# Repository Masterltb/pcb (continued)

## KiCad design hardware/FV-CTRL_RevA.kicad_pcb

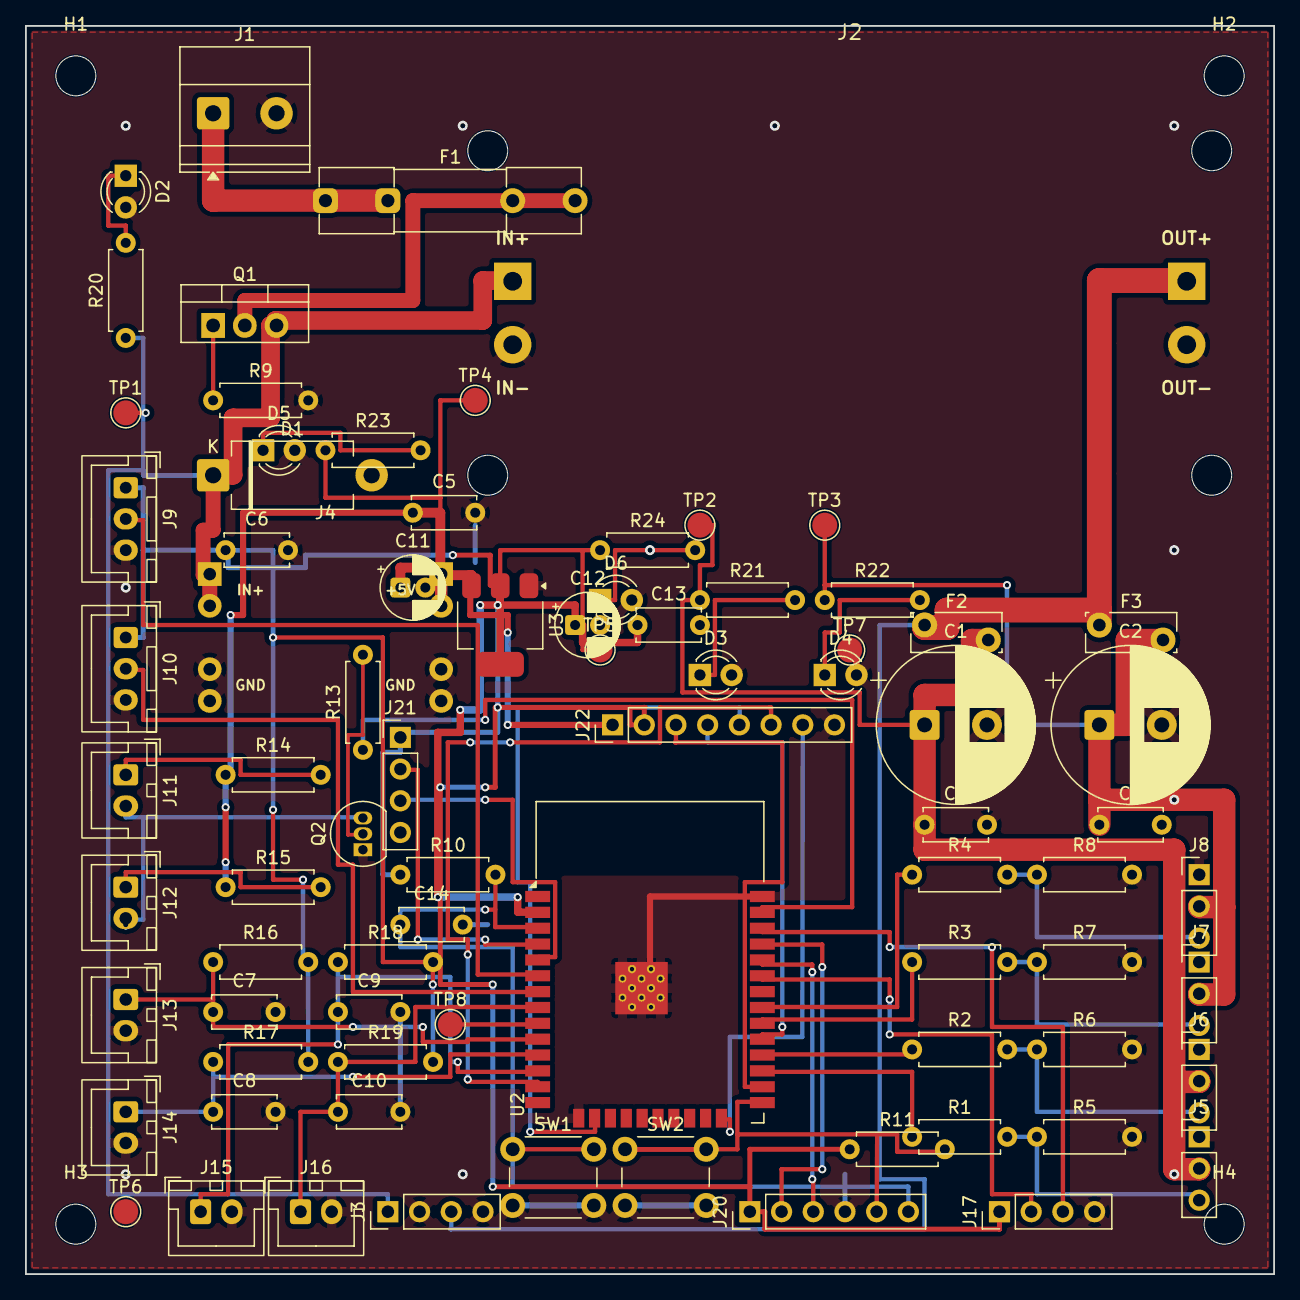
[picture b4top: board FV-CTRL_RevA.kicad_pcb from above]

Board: 2 copper layers, 100.0 x 100.0 mm, 84 parts (0 on the bottom side), 48 nets.

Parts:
C1, C2: 1000-2200uF 16V; CP_Radial_D12.5mm_P5.00mm
C3, C4, C6, C13, C14: 100nF; C_Disc_D5.0mm_W2.5mm_P5.00mm
C5: 10uF 16V; C_Disc_D5.0mm_W2.5mm_P5.00mm
C7, C8, C9, C10: 100nF (DNP); C_Disc_D5.0mm_W2.5mm_P5.00mm
C11: 10uF 16V; CP_Radial_D5.0mm_P2.00mm
C12: 22uF 16V; CP_Radial_D5.0mm_P2.00mm
D1: 1.5KE15CA; D_DO-201_P12.70mm_Horizontal
D2: LED_+12V; LED_D3.0mm
D3: LED_+6V_A; LED_D3.0mm
D4: LED_+6V_B; LED_D3.0mm
D5: LED_+5V; LED_D3.0mm
D6: LED_+3V3; LED_D3.0mm
F1: 5A 250V; Fuseholder_Clip-5x20mm_Littelfuse_111_Inline_P20.00x5.00mm_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
F2, F3: PTC 3A; Fuse_Bourns_MF-RG300
H1, H2, H3, H4: MountingHole_3.2mm_M3
J1: 12V_IN; TerminalBlock_Phoenix_MKDS-1,5-2-5.08_1x02_P5.08mm_Horizont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
J2: XH-M401 (6.0V 8A); Converter_DCDC_XH-M401_8A
J3: AUX_BUCK (DNP); PinHeader_1x04_P2.54mm_Vertical
J4: MP1584EN (5V Logic); Converter_DCDC_MP1584EN
J5: S1_TOP; PinHeader_1x03_P2.54mm_Vertical
J6: S1_BOT; PinHeader_1x03_P2.54mm_Vertical
J7: S2_TOP; PinHeader_1x03_P2.54mm_Vertical
J8: S2_BOT; PinHeader_1x03_P2.54mm_Vertical
J9: IR_RX1; JST_XH_B3B-XH-A_1x03_P2.50mm_Vertical
J10: IR_RX2; JST_XH_B3B-XH-A_1x03_P2.50mm_Vertical
J11: IR_TX1 (Col 1); JST_XH_B2B-XH-A_1x02_P2.50mm_Vertical
J12: IR_TX2 (Col 2); JST_XH_B2B-XH-A_1x02_P2.50mm_Vertical
J13: LS1 (DNP); JST_XH_B2B-XH-A_1x02_P2.50mm_Vertical
J14: LS2 (DNP); JST_XH_B2B-XH-A_1x02_P2.50mm_Vertical
J15: LS3 (DNP); JST_XH_B2B-XH-A_1x02_P2.50mm_Vertical
J16: LS4 (DNP); JST_XH_B2B-XH-A_1x02_P2.50mm_Vertical
J17: I2C_RESERVED; PinHeader_1x04_P2.54mm_Vertical
J20: PROG_UART0; PinHeader_1x06_P2.54mm_Vertical
J21: SENSOR_ADC; PinHeader_1x04_P2.54mm_Vertical
J22: SENSOR_DIGITAL; PinHeader_1x08_P2.54mm_Vertical
Q1: IRF9540N; TO-220-3_Vertical
Q2: S8050; TO-92_Inline
R1, R2, R3, R4: 330R; R_Axial_DIN0207_L6.3mm_D2.5mm_P7.62mm_Horizontal
R5, R6, R7, R8, R9, R10, R11: 10k; R_Axial_DIN0207_L6.3mm_D2.5mm_P7.62mm_Horizontal
R13: 1k; R_Axial_DIN0207_L6.3mm_D2.5mm_P7.62mm_Horizontal
R14, R15: 120R; R_Axial_DIN0207_L6.3mm_D2.5mm_P7.62mm_Horizontal
R16, R17, R18, R19: 10k (DNP); R_Axial_DIN0207_L6.3mm_D2.5mm_P7.62mm_Horizontal
R20: 5.6k; R_Axial_DIN0207_L6.3mm_D2.5mm_P7.62mm_Horizontal
R21, R22: 2.2k; R_Axial_DIN0207_L6.3mm_D2.5mm_P7.62mm_Horizontal
R23: 1.5k; R_Axial_DIN0207_L6.3mm_D2.5mm_P7.62mm_Horizontal
R24: 1.0k; R_Axial_DIN0207_L6.3mm_D2.5mm_P7.62mm_Horizontal
SW1: SW_EN; SW_PUSH_6mm_H5mm
SW2: SW_BOOT; SW_PUSH_6mm_H5mm
TP1: TP_+12V; TestPoint_Pad_D2.0mm
TP2: TP_+6V_A; TestPoint_Pad_D2.0mm
TP3: TP_+6V_B; TestPoint_Pad_D2.0mm
TP4: TP_+5V; TestPoint_Pad_D2.0mm
TP5: TP_+3V3; TestPoint_Pad_D2.0mm
TP6, TP7: TP_GND; TestPoint_Pad_D2.0mm
TP8: TP_SPARE_GPIO33; TestPoint_Pad_D2.0mm
U2: ESP32-WROOM-32; ESP32-WROOM-32_HandSolder
U3: AMS1117-3.3; SOT-223-3_TabPin2

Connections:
+3V3: C6.1, C12.1, C13.1, J9.1, J10.1, J17.1, J20.1, J21.1, J22.2, R10.1, R11.1, R16.2, R17.2, R18.2, R19.2, R24.1, TP5.1, U2.2, U3.2
+5V: C5.1, C11.1, J4.3, J22.1, R14.1, R15.1, R23.1, TP4.1, U3.3
+6V_A: C1.1, C3.1, F2.2, J5.2, J6.2, R21.1, TP2.1
+6V_B: C2.1, C4.1, F3.2, J7.2, J8.2, R22.1, TP3.1
+6V_SERVO: F2.1, F3.1, J2.3, J3.3
+12V: D1.1, J2.1, J3.1, J4.1, Q1.3, R20.1, TP1.1
+12V_FUSED: F1.2, Q1.2
+12V_IN: F1.1, J1.1
ADC_VN: J21.3, U2.5
ADC_VP: J21.2, U2.4
ESP_EN: C14.1, J20.6, R10.2, SW1.1, U2.3
ESP_IO0: J20.5, R11.2, SW2.1, U2.25
ESP_IR_TX: R13.1, U2.37
ESP_RXD0: J20.3, U2.34
ESP_S1_BOT_PWM: R2.1, U2.28
ESP_S1_TOP_PWM: R1.1, U2.27
ESP_S2_BOT_PWM: R4.1, U2.31
ESP_S2_TOP_PWM: R3.1, U2.30
ESP_TXD0: J20.2, U2.35
EXP_IO2: J22.7, U2.24
EXP_IO4: J22.3, U2.26
EXP_IO5: J22.4, U2.29
EXP_IO13: J22.5, U2.16
EXP_IO14: J22.6, U2.13
GND: C1.2, C2.2, C3.2, C4.2, C5.2, C6.2, C7.2, C8.2, C9.2, C10.2, C11.2, C12.2, C13.2, C14.2, D1.2, D2.2, D3.2, D4.2, D5.2, D6.2, J1.2, J2.2, J2.4, J3.2, J3.4, J4.2, J4.4, J5.1, J6.1, J7.1, J8.1, J9.3, J10.3, J13.2, J14.2, J15.2, J16.2, J17.4, J20.4, J21.4, J22.8, Q2.1, R5.2, R6.2, R7.2, R8.2, R9.2, SW1.2, SW2.2, TP6.1, TP7.1, U2.1, U2.15, U2.38, U2.39, U3.1
I2C_SCL: J17.3, U2.36
I2C_SDA: J17.2, U2.33
IR_RX1: J9.2, U2.6
IR_RX2: J10.2, U2.7
IR_TX_RET: J11.2, J12.2, Q2.3
LS1: C7.1, J13.1, R16.1, U2.10
LS2: C8.1, J14.1, R17.1, U2.11
LS3: C9.1, J15.1, R18.1, U2.12
LS4: C10.1, J16.1, R19.1, U2.8
NET_D2_ANODE: D2.1, R20.2
NET_D3_ANODE: D3.1, R21.2
NET_D4_ANODE: D4.1, R22.2
NET_D5_ANODE: D5.1, R23.2
NET_D6_ANODE: D6.1, R24.2
NET_IR_TX1_ANODE: J11.1, R14.2
NET_IR_TX2_ANODE: J12.1, R15.2
NET_Q1_GATE: Q1.1, R9.1
NET_Q2_BASE: Q2.2, R13.2
S1_BOT_PWM: J6.3, R2.2, R6.1
S1_TOP_PWM: J5.3, R1.2, R5.1
S2_BOT_PWM: J8.3, R4.2, R8.1
S2_TOP_PWM: J7.3, R3.2, R7.1
SPARE_GPIO33: TP8.1, U2.9

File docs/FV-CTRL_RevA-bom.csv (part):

Reference,Value,Footprint,DNP,Description,MPN
J1,12V_IN,"TerminalBlock_Phoenix:TerminalBlock_Phoenix_MKDS-1,5-2-5.08_1x02_P5.08mm_Horizontal",No,12V DC input pluggable screw terminal,Pluggable 2-pin 5.0mm
F1,5A 250V,Fuse:Fuseholder_Clip-5x20mm_Littelfuse_111_Inline_P20.00x5.00mm_D1.05mm_Horizontal,No,5A replaceable cartridge fuse in THT socket,5x20mm 5A cartridge
Q1,IRF9540N,Package_TO_SOT_THT:TO-220-3_Vertical,No,P-MOSFET reverse polarity protection,IRF9540NPBF
R9,10k,Resistor_THT:R_Axial_DIN0207_L6.3mm_D2.5mm_P7.62mm_Horizontal,No,P-MOSFET gate-to-GND pull-down resistor,10k 1/4W 5%
D1,1.5KE15CA,Diode_THT:D_DO-201_P12.70mm_Horizontal,No,12V bidirectional TVS overvoltage clamp,1.5KE15CA
J2,XH-M401 (6.0V 8A),fv_modules:Converter_DCDC_XH-M401_8A,No,"XH-M401 (6.0V 8A) header (IN+, IN-, OUT+, OUT-)",XH-M401 (XL4016E1 8A 200W)
J3,AUX_BUCK (DNP),Connector_PinHeader_2.54mm:PinHeader_1x04_P2.54mm_Vertical,Yes,"AUX_BUCK (DNP) header (IN+, IN-, OUT+, OUT-)",Auxiliary 4-pin Header
J4,MP1584EN (5V Logic),fv_modules:Converter_DCDC_MP1584EN,No,"MP1584EN (5V Logic) header (IN+, IN-, OUT+, OUT-)",MP1584EN Mini 3A Buck
F2,PTC 3A,Fuse:Fuse_Bourns_MF-RG300,No,Resettable PTC fuse for Servo Rail A (~3A hold),Bourns MF-R300
C1,1000-2200uF 16V,Capacitor_THT:CP_Radial_D12.5mm_P5.00mm,No,Bulk servo filter capacitor (Rail A),1000uF 16V Radial
C3,100nF,Capacitor_THT:C_Disc_D5.0mm_W2.5mm_P5.00mm,No,High-frequency decoupling (Rail A),100nF 50V Ceramic
J5,S1_TOP,Connector_PinHeader_2.54mm:PinHeader_1x03_P2.54mm_Vertical,No,"Column 1 Top Servo Header (GND, V+, SIG)",3-pin Header
J6,S1_BOT,Connector_PinHeader_2.54mm:PinHeader_1x03_P2.54mm_Vertical,No,"Column 1 Bottom Servo Header (GND, V+, SIG)",3-pin Header
F3,PTC 3A,Fuse:Fuse_Bourns_MF-RG300,No,Resettable PTC fuse for Servo Rail B (~3A hold),Bourns MF-R300
C2,1000-2200uF 16V,Capacitor_THT:CP_Radial_D12.5mm_P5.00mm,No,Bulk servo filter capacitor (Rail B),1000uF 16V Radial
C4,100nF,Capacitor_THT:C_Disc_D5.0mm_W2.5mm_P5.00mm,No,High-frequency decoupling (Rail B),100nF 50V Ceramic
J7,S2_TOP,Connector_PinHeader_2.54mm:PinHeader_1x03_P2.54mm_Vertical,No,"Column 2 Top Servo Header (GND, V+, SIG)",3-pin Header
J8,S2_BOT,Connector_PinHeader_2.54mm:PinHeader_1x03_P2.54mm_Vertical,No,"Column 2 Bottom Servo Header (GND, V+, SIG)",3-pin Header
J18,ESP32_Left (Pins 1-19),Connector_PinSocket_2.54mm:PinSocket_1x19_P2.54mm_Vertical,No,ESP32 DevKit 38 Left 19-pin Socket Header,19-pin Female Header 2.54mm
J19,ESP32_Right (Pins 20-38),Connector_PinSocket_2.54mm:PinSocket_1x19_P2.54mm_Vertical,No,ESP32 DevKit 38 Right 19-pin Socket Header,19-pin Female Header 2.54mm
R1,330R,Resistor_THT:R_Axial_DIN0207_L6.3mm_D2.5mm_P7.62mm_Horizontal,No,330 ohm series protection for S1_TOP_PWM,330R 1/4W 5%
R5,10k,Resistor_THT:R_Axial_DIN0207_L6.3mm_D2.5mm_P7.62mm_Horizontal,No,10k pull-down boot protection for S1_TOP_PWM,10k 1/4W 5%
R2,330R,Resistor_THT:R_Axial_DIN0207_L6.3mm_D2.5mm_P7.62mm_Horizontal,No,330 ohm series protection for S1_BOT_PWM,330R 1/4W 5%
R6,10k,Resistor_THT:R_Axial_DIN0207_L6.3mm_D2.5mm_P7.62mm_Horizontal,No,10k pull-down boot protection for S1_BOT_PWM,10k 1/4W 5%
R3,330R,Resistor_THT:R_Axial_DIN0207_L6.3mm_D2.5mm_P7.62mm_Horizontal,No,330 ohm series protection for S2_TOP_PWM,330R 1/4W 5%
R7,10k,Resistor_THT:R_Axial_DIN0207_L6.3mm_D2.5mm_P7.62mm_Horizontal,No,10k pull-down boot protection for S2_TOP_PWM,10k 1/4W 5%
R4,330R,Resistor_THT:R_Axial_DIN0207_L6.3mm_D2.5mm_P7.62mm_Horizontal,No,330 ohm series protection for S2_BOT_PWM,330R 1/4W 5%
R8,10k,Resistor_THT:R_Axial_DIN0207_L6.3mm_D2.5mm_P7.62mm_Horizontal,No,10k pull-down boot protection for S2_BOT_PWM,10k 1/4W 5%
R13,1k,Resistor_THT:R_Axial_DIN0207_L6.3mm_D2.5mm_P7.62mm_Horizontal,No,Base current limit resistor for IR driver,1k 1/4W 5%
Q2,S8050,Package_TO_SOT_THT:TO-92_Inline,No,NPN driver transistor for 38kHz IR burst transmitter,S8050
R14,120R,Resistor_THT:R_Axial_DIN0207_L6.3mm_D2.5mm_P7.62mm_Horizontal,No,Current limiting resistor for Col 1 IR LED,120R 1/2W 5%
J11,IR_TX1 (Col 1),Connector_JST:JST_XH_B2B-XH-A_1x02_P2.50mm_Vertical,No,Col 1 IR LED Emitter JST-XH 2-pin,JST-XH 2-pin
R15,120R,Resistor_THT:R_Axial_DIN0207_L6.3mm_D2.5mm_P7.62mm_Horizontal,No,Current limiting resistor for Col 2 IR LED,120R 1/2W 5%
J12,IR_TX2 (Col 2),Connector_JST:JST_XH_B2B-XH-A_1x02_P2.50mm_Vertical,No,Col 2 IR LED Emitter JST-XH 2-pin,JST-XH 2-pin
J9,IR_RX1,Connector_JST:JST_XH_B3B-XH-A_1x03_P2.50mm_Vertical,No,"Col 1 IR Receiver header (3V3, OUT, GND)",JST-XH 3-pin
J10,IR_RX2,Connector_JST:JST_XH_B3B-XH-A_1x03_P2.50mm_Vertical,No,"Col 2 IR Receiver header (3V3, OUT, GND)",JST-XH 3-pin
J13,LS1 (DNP),Connector_JST:JST_XH_B2B-XH-A_1x02_P2.50mm_Vertical,Yes,Limit switch LS1 (DNP),JST-XH 2-pin
R16,10k (DNP),Resistor_THT:R_Axial_DIN0207_L6.3mm_D2.5mm_P7.62mm_Horizontal,Yes,10k pull-up for LS1 (DNP),10k 1/4W 5%
C7,100nF (DNP),Capacitor_THT:C_Disc_D5.0mm_W2.5mm_P5.00mm,Yes,100nF filter capacitor for LS1 (DNP),100nF 50V Ceramic
J14,LS2 (DNP),Connector_JST:JST_XH_B2B-XH-A_1x02_P2.50mm_Vertical,Yes,Limit switch LS2 (DNP),JST-XH 2-pin
R17,10k (DNP),Resistor_THT:R_Axial_DIN0207_L6.3mm_D2.5mm_P7.62mm_Horizontal,Yes,10k pull-up for LS2 (DNP),10k 1/4W 5%
C8,100nF (DNP),Capacitor_THT:C_Disc_D5.0mm_W2.5mm_P5.00mm,Yes,100nF filter capacitor for LS2 (DNP),100nF 50V Ceramic
J15,LS3 (DNP),Connector_JST:JST_XH_B2B-XH-A_1x02_P2.50mm_Vertical,Yes,Limit switch LS3 (DNP),JST-XH 2-pin
R18,10k (DNP),Resistor_THT:R_Axial_DIN0207_L6.3mm_D2.5mm_P7.62mm_Horizontal,Yes,10k pull-up for LS3 (DNP),10k 1/4W 5%
C9,100nF (DNP),Capacitor_THT:C_Disc_D5.0mm_W2.5mm_P5.00mm,Yes,100nF filter capacitor for LS3 (DNP),100nF 50V Ceramic
J16,LS4 (DNP),Connector_JST:JST_XH_B2B-XH-A_1x02_P2.50mm_Vertical,Yes,Limit switch LS4 (DNP),JST-XH 2-pin
R19,10k (DNP),Resistor_THT:R_Axial_DIN0207_L6.3mm_D2.5mm_P7.62mm_Horizontal,Yes,10k pull-up for LS4 (DNP),10k 1/4W 5%
C10,100nF (DNP),Capacitor_THT:C_Disc_D5.0mm_W2.5mm_P5.00mm,Yes,100nF filter capacitor for LS4 (DNP),100nF 50V Ceramic
C5,10uF 16V,Capacitor_THT:C_Disc_D5.0mm_W2.5mm_P5.00mm,No,5V rail bulk decoupling capacitor,10uF 16V Radial
C6,100nF,Capacitor_THT:C_Disc_D5.0mm_W2.5mm_P5.00mm,No,3.3V rail decoupling capacitor,100nF 50V Ceramic
R20,5.6k,Resistor_THT:R_Axial_DIN0207_L6.3mm_D2.5mm_P7.62mm_Horizontal,No,Current limiting for +12V LED,5.6k 1/4W 5%
D2,LED_+12V,LED_THT:LED_D3.0mm,No,Green LED indicator for +12V,3mm Green LED
R21,2.2k,Resistor_THT:R_Axial_DIN0207_L6.3mm_D2.5mm_P7.62mm_Horizontal,No,Current limiting for +6V_A LED,2.2k 1/4W 5%
D3,LED_+6V_A,LED_THT:LED_D3.0mm,No,Green LED indicator for +6V_A,3mm Green LED
R22,2.2k,Resistor_THT:R_Axial_DIN0207_L6.3mm_D2.5mm_P7.62mm_Horizontal,No,Current limiting for +6V_B LED,2.2k 1/4W 5%
D4,LED_+6V_B,LED_THT:LED_D3.0mm,No,Green LED indicator for +6V_B,3mm Green LED
R23,1.5k,Resistor_THT:R_Axial_DIN0207_L6.3mm_D2.5mm_P7.62mm_Horizontal,No,Current limiting for +5V LED,1.5k 1/4W 5%
D5,LED_+5V,LED_THT:LED_D3.0mm,No,Green LED indicator for +5V,3mm Green LED
R24,1.0k,Resistor_THT:R_Axial_DIN0207_L6.3mm_D2.5mm_P7.62mm_Horizontal,No,Current limiting for +3V3 LED,1.0k 1/4W 5%
D6,LED_+3V3,LED_THT:LED_D3.0mm,No,Green LED indicator for +3V3,3mm Green LED
TP1,TP_+12V,TestPoint:TestPoint_Pad_D2.0mm,No,Diagnostic Test Point for +12V,Test Point Loop THT
TP2,TP_+6V_A,TestPoint:TestPoint_Pad_D2.0mm,No,Diagnostic Test Point for +6V_A,Test Point Loop THT
TP3,TP_+6V_B,TestPoint:TestPoint_Pad_D2.0mm,No,Diagnostic Test Point for +6V_B,Test Point Loop THT
TP4,TP_+5V,TestPoint:TestPoint_Pad_D2.0mm,No,Diagnostic Test Point for +5V,Test Point Loop THT
TP5,TP_+3V3,TestPoint:TestPoint_Pad_D2.0mm,No,Diagnostic Test Point for +3V3,Test Point Loop THT
TP6,TP_GND,TestPoint:TestPoint_Pad_D2.0mm,No,Diagnostic Test Point for GND,Test Point Loop THT
TP7,TP_GND,TestPoint:TestPoint_Pad_D2.0mm,No,Diagnostic Test Point for GND,Test Point Loop THT
TP8,TP_SPARE_GPIO33,TestPoint:TestPoint_Pad_D2.0mm,No,Diagnostic Test Point for SPARE_GPIO33,Test Point Loop THT
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
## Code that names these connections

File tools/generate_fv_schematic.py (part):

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    sb.record_net("GND", "J5.1", "power")

    sb.add_wire(p_J5_3[0], p_J5_3[1], 198.12, p_J5_3[1])
    sb.add_label("S1_TOP_PWM", 198.12, p_J5_3[1])
    sb.record_net("S1_TOP_PWM", "J5.3", "signal")

    sb.add_wire(p_J6_1[0], p_J6_1[1], 238.76, p_J6_1[1])
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    sb.record_net("GND", "J6.1", "power")

    sb.add_wire(p_J6_3[0], p_J6_3[1], 233.68, p_J6_3[1])
    sb.add_label("S1_BOT_PWM", 233.68, p_J6_3[1])
    sb.record_net("S1_BOT_PWM", "J6.3", "signal")

    # --- RAIL B ---
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    sb.record_net("GND", "J7.1", "power")

    sb.add_wire(p_J7_3[0], p_J7_3[1], 198.12, p_J7_3[1])
    sb.add_label("S2_TOP_PWM", 198.12, p_J7_3[1])
    sb.record_net("S2_TOP_PWM", "J7.3", "signal")

    sb.add_wire(p_J8_1[0], p_J8_1[1], 238.76, p_J8_1[1])
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    sb.record_net("GND", "J8.1", "power")

    sb.add_wire(p_J8_3[0], p_J8_3[1], 233.68, p_J8_3[1])
    sb.add_label("S2_BOT_PWM", 233.68, p_J8_3[1])
    sb.record_net("S2_BOT_PWM", "J8.3", "signal")

    # =========================================================================
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
    # Left Side Pins
    sb.add_wire(p_u2[3][0], p_u2[3][1], 175.26, p_u2[3][1])
    sb.add_label("ESP_EN", 175.26, p_u2[3][1])
    sb.record_net("ESP_EN", "U2.3", "signal")

    sb.add_wire(p_u2[4][0], p_u2[4][1], 175.26, p_u2[4][1])
    sb.add_label("ADC_VP", 175.26, p_u2[4][1])
    sb.record_net("ADC_VP", "U2.4", "signal")

    sb.add_wire(p_u2[5][0], p_u2[5][1], 175.26, p_u2[5][1])
    sb.add_label("ADC_VN", 175.26, p_u2[5][1])
    sb.record_net("ADC_VN", "U2.5", "signal")

    for p_idx in [17, 18, 19, 20, 21, 22, 32]:
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        11: ("LS2", "signal"),
        12: ("LS3", "signal"),
        8:  ("LS4", "signal"),
        9:  ("SPARE_GPIO33", "signal"),
        6:  ("IR_RX1", "signal"),
        7:  ("IR_RX2", "signal"),
    }
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
    sb.add_wire(p_r10_2[0], 157.48, 154.94, 157.48)
    sb.add_junction(154.94, 157.48)
    sb.add_label("ESP_EN", 154.94, 157.48)
    sb.record_net("ESP_EN", "R10.2", "signal")

    sb.add_symbol("Device:C", "C14", "100nF", 154.94, 167.64,
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
    sb.add_wire(p_r11_2[0], 180.34, 154.94, 180.34)
    sb.add_junction(154.94, 180.34)
    sb.add_label("ESP_IO0", 154.94, 180.34)
    sb.record_net("ESP_IO0", "R11.2", "signal")

    sb.add_symbol("Switch:SW_Push", "SW2", "SW_BOOT", 167.64, 180.34,
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    p_R13_2 = get_pin_pos("Device:R", 2, 43.18, 208.28, rot=90)

    sb.add_wire(33.02, 208.28, p_R13_1[0], p_R13_1[1])
    sb.add_label("ESP_IR_TX", 33.02, 208.28)
    sb.record_net("ESP_IR_TX", "R13.1", "signal")

    # Q2: NPN (S8050 / 2N2222) at (55.88, 208.28), rot 0
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    sb.add_wire(p_Q2_C[0], p_Q2_C[1], p_Q2_C[0], 198.12)
    sb.add_wire(p_Q2_C[0], 198.12, 76.2, 198.12)
    sb.add_junction(76.2, 198.12)
    sb.add_label("IR_TX_RET", 66.04, 198.12)
    sb.record_net("IR_TX_RET", "Q2.C", "signal")

    # Channel 1: R14 (120R) + J11 (IR_TX1)
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    sb.record_net("+3V3", "J9.1", "power")

    sb.add_wire(p_J9_2[0], p_J9_2[1], 137.16, p_J9_2[1])
    sb.add_label("IR_RX1", 137.16, p_J9_2[1])
    sb.record_net("IR_RX1", "J9.2", "signal")

    sb.add_wire(p_J9_3[0], p_J9_3[1], 137.16, p_J9_3[1])
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    sb.record_net("+3V3", "J10.1", "power")

    sb.add_wire(p_J10_2[0], p_J10_2[1], 137.16, p_J10_2[1])
    sb.add_label("IR_RX2", 137.16, p_J10_2[1])
    sb.record_net("IR_RX2", "J10.2", "signal")

    sb.add_wire(p_J10_3[0], p_J10_3[1], 137.16, p_J10_3[1])
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        ("TP5", "+3V3", 355.6, 162.56),
        ("TP6", "GND", 355.6, 187.96),
        ("TP7", "GND", 381.0, 187.96),
        ("TP8", "SPARE_GPIO33", 381.0, 162.56),
    ]

    for tp_ref, rail, x_pos, y_pos in test_points:
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    sb.record_net("+3V3", "J17.1", "power")

    sb.add_wire(p_i2c_2[0], p_i2c_2[1], 314.96, p_i2c_2[1])
    sb.add_label("I2C_SDA", 314.96, p_i2c_2[1])
    sb.record_net("I2C_SDA", "J17.2", "signal")

    sb.add_wire(p_i2c_3[0], p_i2c_3[1], 314.96, p_i2c_3[1])
    sb.add_label("I2C_SCL", 314.96, p_i2c_3[1])
    sb.record_net("I2C_SCL", "J17.3", "signal")

    sb.add_wire(p_i2c_4[0], p_i2c_4[1], 314.96, p_i2c_4[1])
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            {"ref": "J2", "value": "XL4015_A", "pins": ["+12V", "GND", "+6V_A", "GND"]},
            {"ref": "J3", "value": "XL4015_B", "pins": ["+12V", "GND", "+6V_B", "GND"]},
            {"ref": "J4", "value": "BUCK_5V", "pins": ["+12V", "GND", "+5V", "GND"]},
            {"ref": "J5", "value": "S1_TOP", "pins": ["GND", "+6V_A", "S1_TOP_PWM"]},
            {"ref": "J6", "value": "S1_BOT", "pins": ["GND", "+6V_A", "S1_BOT_PWM"]},
            {"ref": "J7", "value": "S2_TOP", "pins": ["GND", "+6V_B", "S2_TOP_PWM"]},
            {"ref": "J8", "value": "S2_BOT", "pins": ["GND", "+6V_B", "S2_BOT_PWM"]},
            {"ref": "J9", "value": "IR_RX1", "pins": ["+3V3", "IR_RX1", "GND"]},
            {"ref": "J10", "value": "IR_RX2", "pins": ["+3V3", "IR_RX2", "GND"]}
        ],
        "signals": {
            "S1_TOP_PWM": "GPIO16",
            "S1_BOT_PWM": "GPIO17",
            "S2_TOP_PWM": "GPIO18",
            "S2_BOT_PWM": "GPIO19",
            "IR_TX": "GPIO23",
            "IR_RX1": "GPIO34",
            "IR_RX2": "GPIO35",
            "LS1": "GPIO25",
            "LS2": "GPIO26",
            "LS3": "GPIO27",
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
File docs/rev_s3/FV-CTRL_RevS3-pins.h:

/**
 * @file FV-CTRL_RevS3-pins.h
 * @brief FreshVend Controller Rev-S3 Board Pin Definitions & Hardware Configuration
 * @author FreshVend Hardware Engineering Team
 * @date 2026-10-28
 *
 * Microcontroller: ESP32-S3-WROOM-1U (Dual-core Xtensa LX7 @ 240MHz, 8MB Flash, IPEX Ant)
 * Hardware Revision: Rev-S3
 * Target Application: Automated Fresh Fruit Bowl Vending Machine Controller
 */

#ifndef FV_CTRL_REVS3_PINS_H_
#define FV_CTRL_REVS3_PINS_H_

#include <stdint.h>

#ifdef __cplusplus
extern "C" {
#endif

/* ========================================================================== */
/*                               BOARD METADATA                               */
/* ========================================================================== */
#define FV_BOARD_REVISION           "Rev-S3"
#define FV_BOARD_MCU                "ESP32-S3-WROOM-1U"
#define FV_BOARD_FLASH_SIZE_MB      8
#define FV_BOARD_NATIVE_USB         1

/* ========================================================================== */
/*                           SERVO ACTUATOR PWM PINS                          */
/* ========================================================================== */
/**
 * @brief 4x Servo PWM control channels (Standard 50Hz RC PWM, 1.0ms - 2.0ms pulse)
 * Connected via 330 ohm series damping resistors with 10k pulldown resistors.
 * Powered by dedicated +6V Buck converters (+6V_A for Gate 1, +6V_B for Gate 2).
 */
#define PIN_SERVO1_TOP_PWM          16   /* IO16 (Pin 9)  - S1 Top Gate Door Actuator */
#define PIN_SERVO1_BOT_PWM          17   /* IO17 (Pin 10) - S1 Bottom Dispense Actuator */
#define PIN_SERVO2_TOP_PWM          18   /* IO18 (Pin 11) - S2 Top Gate Door Actuator */
#define PIN_SERVO2_BOT_PWM          14   /* IO14 (Pin 22) - S2 Bottom Dispense Actuator */

#define SERVO_PWM_FREQUENCY_HZ      50
#define SERVO_PWM_RESOLUTION_BITS   16

/* ========================================================================== */
/*                      UNIVERSAL DROP DETECTION SENSORS                      */
/* ========================================================================== */
/**
 * @brief Dual Universal 4-Pin Drop Detection Sensor Headers (J11 & J12).
 * JST-XH 4-Pin Layout: [Pin 1: +5V, Pin 2: TRIG, Pin 3: SENS_OUT, Pin 4: GND]
 *
 * Compatible Sensors:
 * 1. SW-420 Vibration Sensor: Digital pulse on SENS_OUT when fruit bowl hits chute.
 * 2. HC-SR04 Ultrasonic Sensor: TRIG sent on PIN_DROP_TRIG, Echo received on PIN_DROP_SENSx.
 * 3. IR Optical Beam Barrier: Active-LOW beam break on PIN_DROP_SENSx.
 *
 * Note: Echo / Sense signals are level-shifted via 1k / 2k divider (5V -> 3.3V safe).
 */
#define PIN_DROP_SENS1              4    /* IO4  (Pin 4)  - Chute 1 Sensor Input (Echo/Digital) */
#define PIN_DROP_SENS2              5    /* IO5  (Pin 5)  - Chute 2 Sensor Input (Echo/Digital) */
#define PIN_DROP_TRIG               21   /* IO21 (Pin 23) - Shared Ultrasonic Trigger Pulse */

/* ========================================================================== */
/*                            LIMIT SWITCH INPUTS                             */
/* ========================================================================== */
/**
 * @brief 4x Endstop Limit Switches for mechanical travel verification (J10 header).
 * Normally-Closed (NC) or Normally-Open (NO) configuration with internal pull-up enabled.
 */
#define PIN_LIMIT_1_TOP             6    /* IO6  (Pin 6)  - Gate 1 Upper Limit Switch */
#define PIN_LIMIT_1_BOT             7    /* IO7  (Pin 7)  - Gate 1 Lower Limit Switch */
#define PIN_LIMIT_2_TOP             8    /* IO8  (Pin 12) - Gate 2 Upper Limit Switch */
#define PIN_LIMIT_2_BOT             9    /* IO9  (Pin 17) - Gate 2 Lower Limit Switch */

/* ========================================================================== */
/*                            I2C EXPANSION BUS                               */
/* ========================================================================== */
/**
 * @brief Spare I2C bus header (J9) with on-board 4.7k pull-up resistors to +3.3V.
 * JST-XH 4-Pin: [Pin 1: +3.3V, Pin 2: SDA, Pin 3: SCL, Pin 4: GND]
 * Ideal for OLED display, temperature/humidity sensor (SHT40), or NFC/RFID reader.
 */
#define PIN_I2C_SDA                 1    /* IO1  (Pin 39) - I2C Data */
#define PIN_I2C_SCL                 2    /* IO2  (Pin 38) - I2C Clock */
#define I2C_BUS_DEFAULT_FREQ_HZ     400000

/* ========================================================================== */
/*                       NATIVE USB & DEBUG UART INTERFACES                   */
/* ========================================================================== */
/**
 * @brief ESP32-S3 Built-in USB-Serial-JTAG on USB Type-C Receptacle (J21).
 * Completely eliminates external USB-UART bridge chips (CP2102N/CH340).
 * Provides direct high-speed flashing, USB CDC console, and hardware JTAG debugging.
 */
#define PIN_USB_DM                  19   /* IO19 (Pin 13) - USB Full-Speed D- */
#define PIN_USB_DP                  20   /* IO20 (Pin 14) - USB Full-Speed D+ */

/**
 * @brief Hardware UART0 Test Points (TP7: TXD, TP8: RXD) for low-level boot logs.
 */
#define PIN_UART0_TX                43   /* IO43 (Pin 37) - Boot Log TX (TP7) */
#define PIN_UART0_RX                44   /* IO44 (Pin 36) - Boot Log RX (TP8) */
#define UART0_DEFAULT_BAUD          115200

/* ========================================================================== */
/*                           SYSTEM CONTROL PUSHBUTTONS                       */
/* ========================================================================== */
#define PIN_ESP_EN                  -1   /* Hardware Reset (EN pin 3, SW1 tact switch) */
#define PIN_ESP_BOOT                0    /* IO0 (Pin 27, SW2 tact switch) - Download mode */

/* ========================================================================== */
/*                           DIAGNOSTIC TEST POINTS                           */
/* ========================================================================== */
#define TP_12V_MAIN                 1    /* TP1 - Main DC +12V post-Schottky */
#define TP_6V_BUCK_A                2    /* TP2 - Servo Gate 1 Power (+6.0V 3A) */
#define TP_6V_BUCK_B                3    /* TP3 - Servo Gate 2 Power (+6.0V 3A) */
#define TP_5V_RECOM                 4    /* TP4 - Logic/Sensor +5.0V (RECOM R-78E5.0) */
#define TP_3V3_MCU                  5    /* TP5 - MCU Power Rail (+3.3V 800mA LD1117) */
#define TP_GND_MAIN                 6    /* TP6 - System Star Ground reference */
#define TP_UART_TX                  7    /* TP7 - Hardware UART0 TX */
#define TP_UART_RX                  8    /* TP8 - Hardware UART0 RX */

/* ========================================================================== */
/*                              HELPER MACROS                                 */
/* ========================================================================== */
#define FV_INIT_INPUTS() do { \
    pinMode(PIN_DROP_SENS1, INPUT); \
    pinMode(PIN_DROP_SENS2, INPUT); \
    pinMode(PIN_LIMIT_1_TOP, INPUT_PULLUP); \
    pinMode(PIN_LIMIT_1_BOT, INPUT_PULLUP); \
    pinMode(PIN_LIMIT_2_TOP, INPUT_PULLUP); \
    pinMode(PIN_LIMIT_2_BOT, INPUT_PULLUP); \
} while(0)

#define FV_INIT_OUTPUTS() do { \
    pinMode(PIN_DROP_TRIG, OUTPUT); \
    digitalWrite(PIN_DROP_TRIG, LOW); \
} while(0)

#ifdef __cplusplus
}
#endif

#endif /* FV_CTRL_REVS3_PINS_H_ */

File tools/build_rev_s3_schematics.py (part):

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r11_p2 = get_pin_pos("Device:R", 2, 96.52, 60.96, 90)
s2_content.append(format_wire(usbc_p_dma[0], usbc_p_dma[1], r11_p1[0], usbc_p_dma[1]))
s2_content.append(format_wire(r11_p1[0], usbc_p_dma[1], r11_p1[0], r11_p1[1]))
s2_content.append(format_global_label("USB_DM_S3", r11_p2[0] + 5.08, r11_p2[1], 0))
s2_content.append(format_wire(r11_p2[0], r11_p2[1], r11_p2[0] + 5.08, r11_p2[1]))

# Connect D+ (A6 & B6 joined) -> R12 22R
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r12_p2 = get_pin_pos("Device:R", 2, 96.52, 73.66, 90)
s2_content.append(format_wire(usbc_p_dpa[0], usbc_p_dpa[1], r12_p1[0], usbc_p_dpa[1]))
s2_content.append(format_wire(r12_p1[0], usbc_p_dpa[1], r12_p1[0], r12_p1[1]))
s2_content.append(format_global_label("USB_DP_S3", r12_p2[0] + 5.08, r12_p2[1], 0))
s2_content.append(format_wire(r12_p2[0], r12_p2[1], r12_p2[0] + 5.08, r12_p2[1]))

# Reset SW1 (at 127.0, 114.3) & Boot SW2 (at 127.0, 144.78)
s2_content.append(format_symbol_instance("Switch:SW_Push", "SW1", "RESET", "Button_Switch_SMD:SW_Push_SPST_NO_Alps_SKRK", 127.0, 114.3))
sw1_p1 = get_pin_pos("Switch:SW_Push", 1, 127.0, 114.3)
sw1_p2 = get_pin_pos("Switch:SW_Push", 2, 127.0, 114.3)
s2_content.append(format_global_label("ESP_EN", sw1_p1[0] - 5.08, sw1_p1[1], 180))
s2_content.append(format_wire(sw1_p1[0], sw1_p1[1], sw1_p1[0] - 5.08, sw1_p1[1]))
s2_content.append(format_global_label("GND", sw1_p2[0] + 5.08, sw1_p2[1], 0))
s2_content.append(format_wire(sw1_p2[0], sw1_p2[1], sw1_p2[0] + 5.08, sw1_p2[1]))
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r10_p1 = get_pin_pos("Device:R", 1, 101.6, 106.68)
r10_p2 = get_pin_pos("Device:R", 2, 101.6, 106.68)
s2_content.append(format_global_label("+3V3", r10_p1[0], r10_p1[1], 180))
s2_content.append(format_global_label("ESP_EN", r10_p2[0], r10_p2[1], 180))

s2_content.append(format_symbol_instance("Device:C", "C10", "1uF", "Capacitor_SMD:C_0603_1608Metric", 101.6, 121.92))
c10_p1 = get_pin_pos("Device:C", 1, 101.6, 121.92)
c10_p2 = get_pin_pos("Device:C", 2, 101.6, 121.92)
s2_content.append(format_global_label("ESP_EN", c10_p1[0], c10_p1[1], 180))
s2_content.append(format_global_label("GND", c10_p2[0], c10_p2[1], 180))

# Boot SW2
s2_content.append(format_symbol_instance("Switch:SW_Push", "SW2", "BOOT", "Button_Switch_SMD:SW_Push_SPST_NO_Alps_SKRK", 127.0, 144.78))
sw2_p1 = get_pin_pos("Switch:SW_Push", 1, 127.0, 144.78)
sw2_p2 = get_pin_pos("Switch:SW_Push", 2, 127.0, 144.78)
s2_content.append(format_global_label("ESP_BOOT", sw2_p1[0] - 5.08, sw2_p1[1], 180))
s2_content.append(format_wire(sw2_p1[0], sw2_p1[1], sw2_p1[0] - 5.08, sw2_p1[1]))
s2_content.append(format_global_label("GND", sw2_p2[0] + 5.08, sw2_p2[1], 0))
s2_content.append(format_wire(sw2_p2[0], sw2_p2[1], sw2_p2[0] + 5.08, sw2_p2[1]))
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    s4_content.append(format_global_label("+5V", p1[0] - 5.08, p1[1], 180))
    s4_content.append(format_wire(p1[0], p1[1], p1[0] - 5.08, p1[1]))

    s4_content.append(format_global_label("DROP_TRIG", p2[0] - 5.08, p2[1], 180))
    s4_content.append(format_wire(p2[0], p2[1], p2[0] - 5.08, p2[1]))

    # Level shift / protection divider: R_div1 (1k series), R_div2 (2k pull-down)
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j9_p4 = get_pin_pos("Connector_Generic:Conn_01x04", 4, 203.2, 63.5)
s5_content.append(format_global_label("+3V3", j9_p1[0] - 5.08, j9_p1[1], 180))
s5_content.append(format_wire(j9_p1[0], j9_p1[1], j9_p1[0] - 5.08, j9_p1[1]))
s5_content.append(format_global_label("I2C_SDA", j9_p2[0] - 5.08, j9_p2[1], 180))
s5_content.append(format_wire(j9_p2[0], j9_p2[1], j9_p2[0] - 5.08, j9_p2[1]))
s5_content.append(format_global_label("I2C_SCL", j9_p3[0] - 5.08, j9_p3[1], 180))
s5_content.append(format_wire(j9_p3[0], j9_p3[1], j9_p3[0] - 5.08, j9_p3[1]))
s5_content.append(format_global_label("GND", j9_p4[0] - 5.08, j9_p4[1], 180))
s5_content.append(format_wire(j9_p4[0], j9_p4[1], j9_p4[0] - 5.08, j9_p4[1]))
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j10_p2 = get_pin_pos("Connector_Generic:Conn_01x04", 2, 279.4, 63.5)
j10_p3 = get_pin_pos("Connector_Generic:Conn_01x04", 3, 279.4, 63.5)
j10_p4 = get_pin_pos("Connector_Generic:Conn_01x04", 4, 279.4, 63.5)
s5_content.append(format_global_label("LIMIT_1_TOP", j10_p1[0] - 5.08, j10_p1[1], 180))
s5_content.append(format_wire(j10_p1[0], j10_p1[1], j10_p1[0] - 5.08, j10_p1[1]))
s5_content.append(format_global_label("LIMIT_1_BOT", j10_p2[0] - 5.08, j10_p2[1], 180))
s5_content.append(format_wire(j10_p2[0], j10_p2[1], j10_p2[0] - 5.08, j10_p2[1]))
s5_content.append(format_global_label("LIMIT_2_TOP", j10_p3[0] - 5.08, j10_p3[1], 180))
s5_content.append(format_wire(j10_p3[0], j10_p3[1], j10_p3[0] - 5.08, j10_p3[1]))
s5_content.append(format_global_label("LIMIT_2_BOT", j10_p4[0] - 5.08, j10_p4[1], 180))
s5_content.append(format_wire(j10_p4[0], j10_p4[1], j10_p4[0] - 5.08, j10_p4[1]))

# Pullups for I2C (R26, R27 4.7k)
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r26_p1 = get_pin_pos("Device:R", 1, 228.6, 50.8)
r26_p2 = get_pin_pos("Device:R", 2, 228.6, 50.8)
s5_content.append(format_global_label("+3V3", r26_p1[0], r26_p1[1], 180))
s5_content.append(format_global_label("I2C_SDA", r26_p2[0], r26_p2[1], 180))

s5_content.append(format_symbol_instance("Device:R", "R27", "4.7k", "Resistor_SMD:R_0603_1608Metric", 243.84, 50.8))
r27_p1 = get_pin_pos("Device:R", 1, 243.84, 50.8)
r27_p2 = get_pin_pos("Device:R", 2, 243.84, 50.8)
s5_content.append(format_global_label("+3V3", r27_p1[0], r27_p1[1], 180))
s5_content.append(format_global_label("I2C_SCL", r27_p2[0], r27_p2[1], 180))

(OUT_DIR / "FV-CTRL_RevS3-05.kicad_sch").write_text(make_sheet("5. Diagnostics & Spares", s5_syms, "\n".join(s5_content)), encoding="utf-8")
print("All 5 sheets + root successfully written to:", OUT_DIR)
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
